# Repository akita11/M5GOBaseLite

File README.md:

# M5GOBaseLite

M5Stackの上部本体(Core/Core2)にとりつけて、以下のようなM5GO/Fireの機能やそれ以外の機能を追加できる底板（ベースボード）用の拡張基板です。
- Groveコネクタ(PortA(2個), PortB, PortC, PortD, PortE)（PortA/B/CはM5Stack純正のものと同等です。PortD/EはM5Stack純正品にはありませんが、UI Flowで使用することができるポートです）
- 左右5個ずつのNeoPixel (SK6812)
- LiPoバッテリ接続端子

# 使い方
1. M5Stackの本体(Core、底板を外した状態)に本ボードを差し込みます。
2. M5Stackのプログラムから、Groveコネクタに接続したセンサ類や左右のNeoPixelを使用します。
   - 左右のNeoPixelの制御信号はGPIO15につながっています。UI Flowでは、Hardware→RGB LED、から使用できます
   - 各Groveコネクタのピン配置は以下の通り（中央寄りのVDDから近い側、遠い側の順）
     - PortA: GPIO21(SDA), GPIO22(SCL)
     - PortB: GPIO26, GPIO36
     - PortC: GPIO17(TXD2), GPIO16(RXD2) (Core2ではGPIO14(TXD2), GPIO13(RXD2))
     - PortD: GPIO35, GPIO34
     - PortE: GPIO13, GPIO5 (Core2ではGPIO19, GPIO33)

※2020/9/4現在、Core2のUIFlowではPortB, C, D, Eは選択できませんので、ポート割当でCustomを選択し、上記のIOピンを指定してください。

# 底面カバー

M5GOBaseLite_cover.svgを厚さ5mmのアクリル板等でカットすると、底面カバーにできます。

# Author

Junichi Akita (@akita11, akita@ifdl.jp)

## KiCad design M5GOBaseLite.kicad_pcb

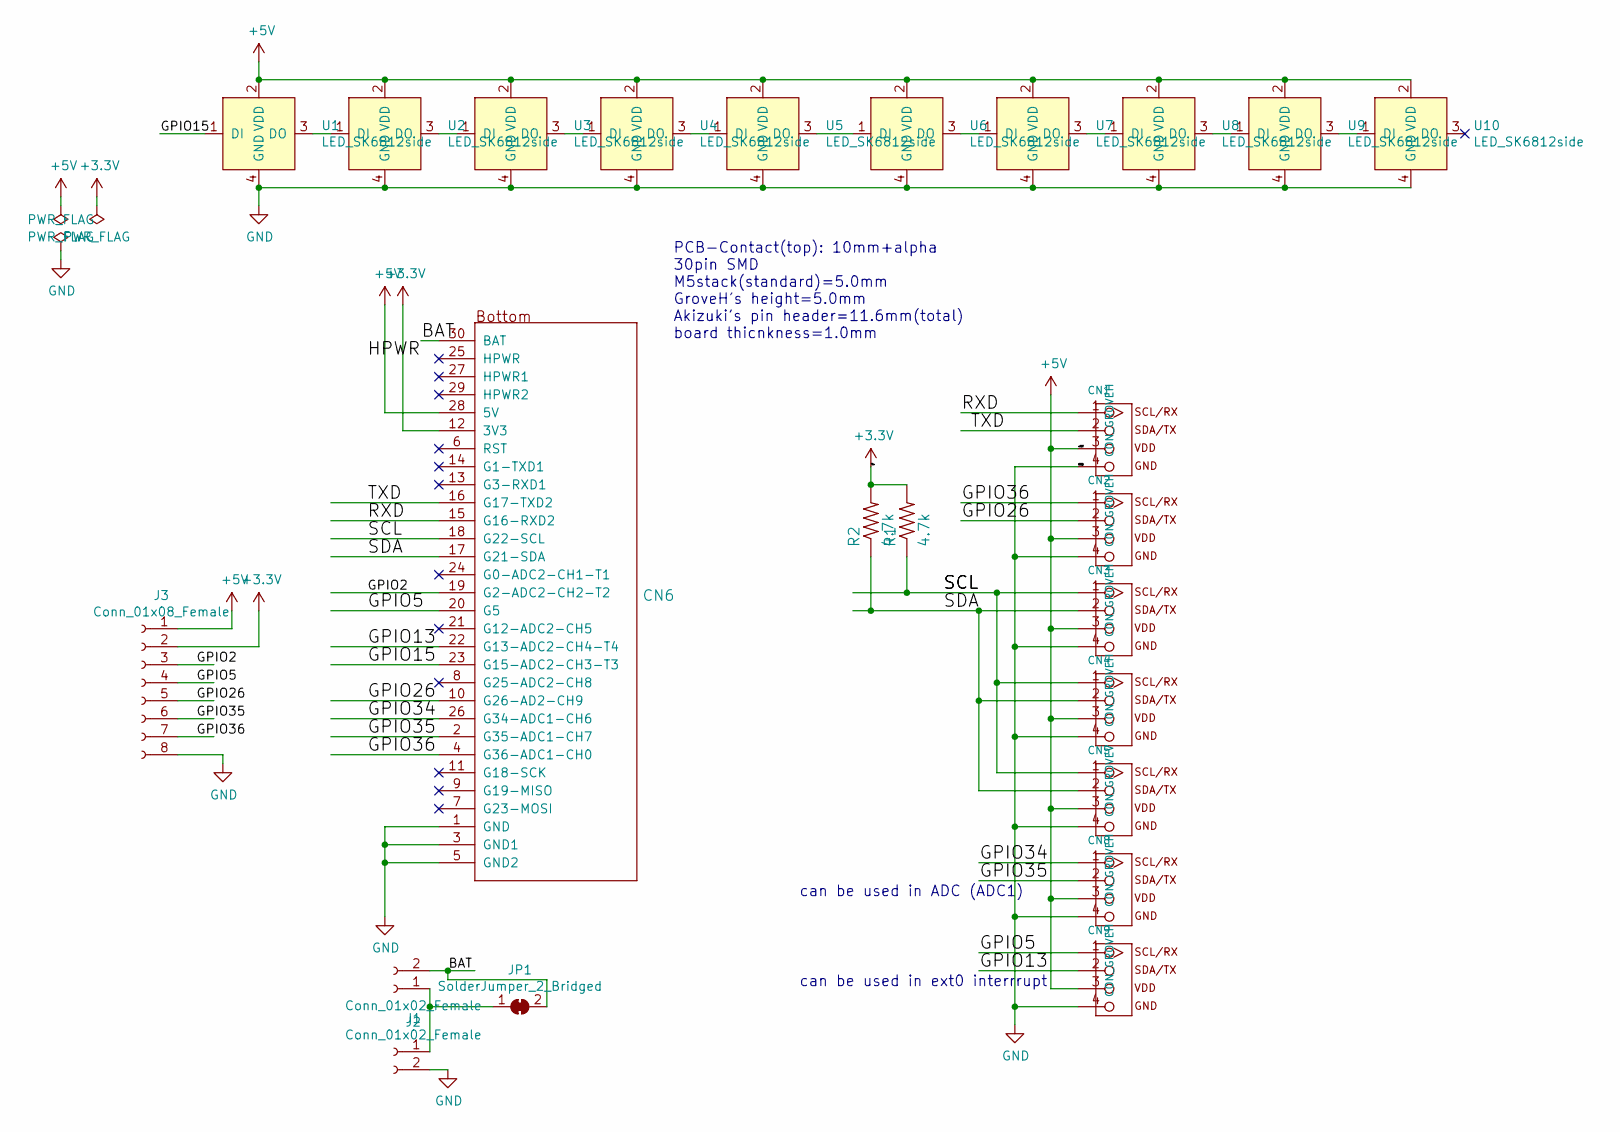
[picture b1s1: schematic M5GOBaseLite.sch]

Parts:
CN1, CN2, CN3, CN4, CN8, CN9: CON_GROVEH; CON_GROVE_H
CN5: CON_GROVEV; CON_GROVE_V
CN6: MBUS_bottom; PinSocket_2x15_P2.54mm_Vertical_SMD
J1: Conn_01x02_Female; JST_PH_S2B-PH-K_1x02_P2.00mm_Horizontal
J2: Conn_01x02_Female; PinHeader_1x02_P2.54mm_Horizontal
J3: Conn_01x08_Female; PinSocket_1x08_P2.54mm_Horizontal
JP1: SolderJumper_2_Bridged; SolderJumper-2_P1.3mm_Bridged_Pad1.0x1.5mm
R1, R2: 4.7k; 0603
U1, U2, U3, U4, U5, U6, U7, U8, U9, U10: LED_SK6812side; LED_SK6812SIDE

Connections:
+3V3: CN6.12 (3V3), J3.2, R1.2, R2.2
+5V: CN1.3, CN2.3, CN3.3, CN4.3, CN5.3, CN6.28 (5V), CN8.3, CN9.3, J3.1, U1.2 (VDD), U2.2 (VDD), U3.2 (VDD), U4.2 (VDD), U5.2 (VDD), U6.2 (VDD), U7.2 (VDD), U8.2 (VDD), U9.2 (VDD), U10.2 (VDD)
/BAT: CN6.30 (BAT), J2.2, JP1.2 (B)
/GPIO2: CN6.19 (G2-ADC2-CH2-T2), J3.3
/GPIO5: CN6.20 (G5), CN9.1, J3.4
/GPIO13: CN6.22 (G13-ADC2-CH4-T4), CN9.2
/GPIO15: CN6.23 (G15-ADC2-CH3-T3), U1.1 (DI)
/GPIO26: CN2.2, CN6.10 (G26-AD2-CH9), J3.5
/GPIO34: CN6.26 (G34-ADC1-CH6), CN8.1
/GPIO35: CN6.2 (G35-ADC1-CH7), CN8.2, J3.6
/GPIO36: CN2.1, CN6.4 (G36-ADC1-CH0), J3.7
/RXD: CN1.1, CN6.15 (G16-RXD2)
/SCL: CN3.1, CN4.1, CN5.1, CN6.18 (G22-SCL), R1.1
/SDA: CN3.2, CN4.2, CN5.2, CN6.17 (G21-SDA), R2.1
/TXD: CN1.2, CN6.16 (G17-TXD2)
GND: CN1.4, CN2.4, CN3.4, CN4.4, CN5.4, CN6.1 (GND), CN6.3 (GND1), CN6.5 (GND2), CN8.4, CN9.4, J1.2, J3.8, U1.4 (GND), U2.4 (GND), U3.4 (GND), U4.4 (GND), U5.4 (GND), U6.4 (GND), U7.4 (GND), U8.4 (GND), U9.4 (GND), U10.4 (GND)
unnamed: J1.1, J2.1, JP1.1 (A)
unnamed: U1.3 (DO), U2.1 (DI)
unnamed: U2.3 (DO), U3.1 (DI)
unnamed: U3.3 (DO), U4.1 (DI)
unnamed: U4.3 (DO), U5.1 (DI)
unnamed: U5.3 (DO), U6.1 (DI)
unnamed: U6.3 (DO), U7.1 (DI)
unnamed: U7.3 (DO), U8.1 (DI)
unnamed: U8.3 (DO), U9.1 (DI)
unnamed: U9.3 (DO), U10.1 (DI)

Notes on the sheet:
can be used in ext0 interrrupt
can be used in ADC (ADC1)
PCB-Contact(top): 10mm+alpha 30pin SMD M5stack(standard)=5.0mm GroveH's height=5.0mm Akizuki's pin header=11.6mm(total) board thicnkness=1.0mm

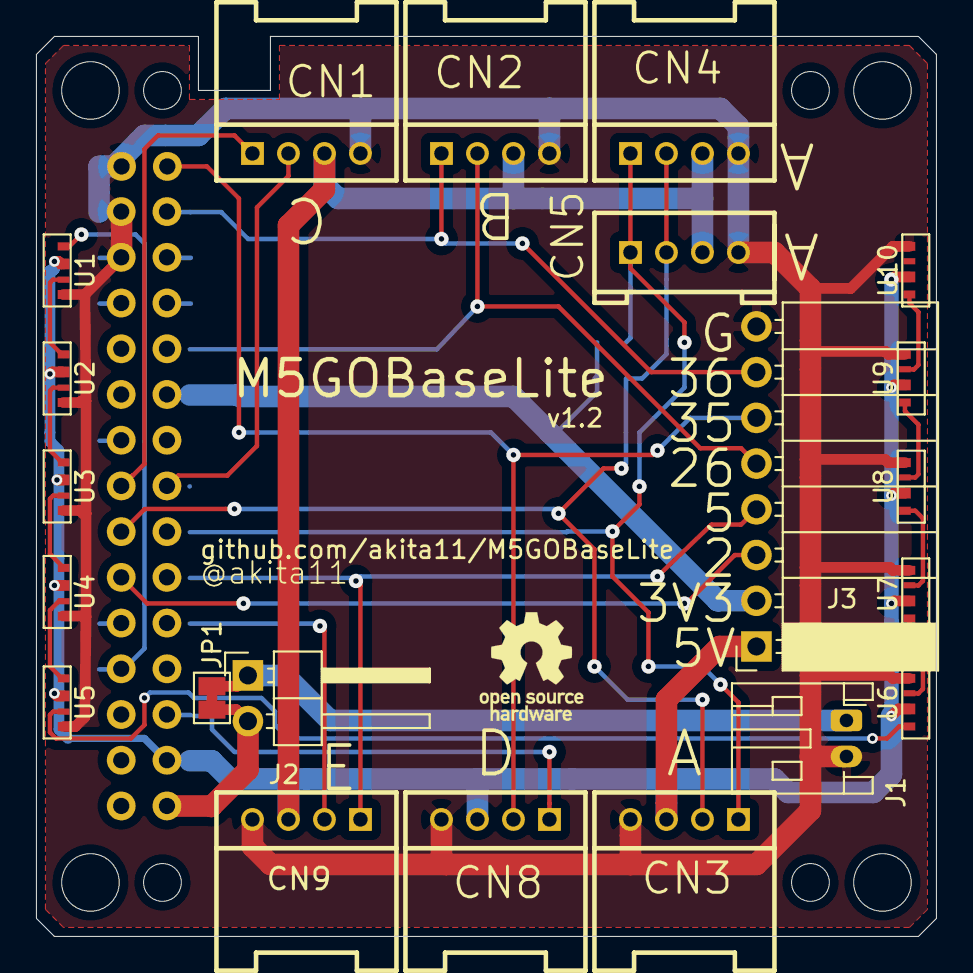
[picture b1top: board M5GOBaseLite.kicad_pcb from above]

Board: 2 copper layers, 50.0 x 50.0 mm, 32 parts (0 on the bottom side), 26 nets.

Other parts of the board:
MH1, MH1#2, MH1#3, MH2: MountingHole_3.2mm_M3
MH5, MH5#2, MH5#3, MH5#4: MountingHole_2.1mm

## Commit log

2020-03-26 ファイル一式の追加、READMEの追記
2020-03-27 カバーのデータを追加
2020-03-27 カバーつきの写真を追加
2020-03-27 写真のファイル名を修正
2020-04-08 カバーのデータの追加
2020-04-22 カバーの細い側が切れやすいのでマージンを太めに
2020-04-26 カバーのカット部を微調整
2020-09-04 Core2の情報を記載
